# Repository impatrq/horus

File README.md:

<div align="center">
    
# [HORUS](https://linktr.ee/agro_horus)

&nbsp;

| Página web | Email | Instagram | YouTube |
|------------|-------|-----------|---------|
|[agro_horus.app](https://horus-pagina-web.vercel.app)|agroohoruss@gmail.com|[@agro_horus](https://www.instagram.com/agro_horus/)|[agro_horus.video](https://www.youtube.com/watch?v=Mp89aknXm1M&pp=ygUaaG9ydXMgcm9ib3Qgc2VtaWF1dG9tYXRpY28%3D)|

&nbsp;

</div>

## ¿Qué es Horus?
Horus es un robot de reconocimiento para el campo que permite la detección de plagas de manera remota.

## ¿De dónde surgió la idea?

Comenzamos primero con la idea de ayudar al campo, luego de investigación llegamos a las problemáticas que presentaban las plagas artrópodos en las plantaciones, así llegamos a la conclusión de automatizar el monitoreo de plantaciones con un robot autónomo.

## ¿Cómo funciona?
El robot se translada de manera autónoma por el campo y analiza los cultivos a su alrededor con una cámara. La IA del robot analiza el video que percibe con la cámara y determina si se encuentra con una plaga. Esta información es luego transmitida por radiofrecuencia a un módulo de comunicación que permite conectarlo a una computadora con nuestra aplicación. Esto incluye base de datos para guardar las detecciones, interfaz gráfica e interacción con el robot para el usuario

## ¿Quiénes somos?

Somos un grupo de alumnos de E.E.S.T. N°7 "Taller Regional Quilmes" (IMPA).

<div align="center">

</div>

### Cabrera, Martín

* 📧 martincabreracirco@gmail.com

* LinkedIn: https://www.linkedin.com/in/mart%C3%ADn-alejandro-cabrera-6014b727b/

### Contreras, Abril Victoria

* 📷 Instagram: @_ _viicontreras__

* 📧 abrilchiscontreras@gmail.com

* LinkedIn: https://www.linkedin.com/in/abril-contreras-039998303/

### Díaz Steinbrecher, Lara

* 📧 diazsteinbrecher@gmail.com

* LinkedIn: https://www.linkedin.com/in/lara-diaz-steinbrecher-97263b303/

### Ferrante, Santino

* 📧 ferrantesantino14@gmail.com
  
* LinkedIn: https://www.linkedin.com/in/santino-marco-ferrante-a57bb5180/

### Kearney, Mateo

* LinkedIn: https://www.linkedin.com/in/mateo-kearney-996637303/

### Torres, Juan Ignacio

* 📧 juanignaciotorr@gmail.com

* LinkedIn: https://www.linkedin.com/in/juan-ignacio-torres-34a232303/

## Reconocimientos

* Medalla de Oro en PROTOTIPOS - EJE LIBRE de las ONIET 2024

* Medalla de Oro en FEED DE INSTAGRAM de las ONIET 2024

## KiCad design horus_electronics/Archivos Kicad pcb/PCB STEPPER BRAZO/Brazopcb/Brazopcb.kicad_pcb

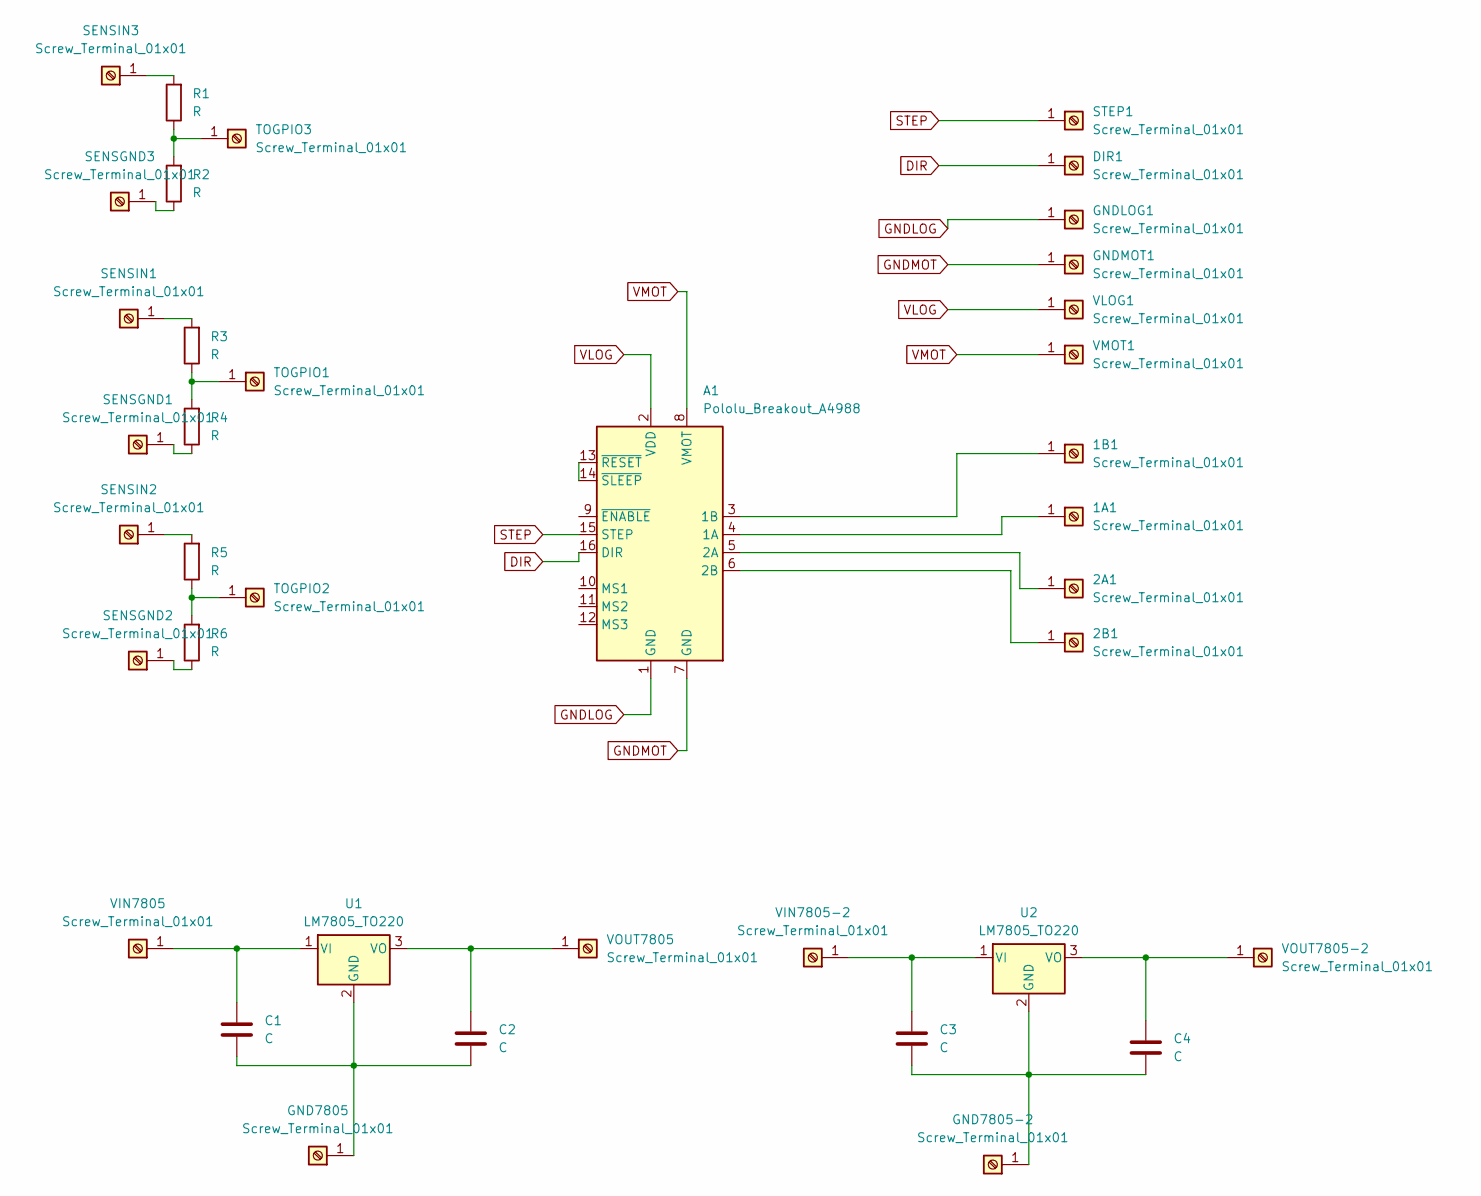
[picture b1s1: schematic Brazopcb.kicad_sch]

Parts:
1A1, 1B1, 2A1, 2B1: Screw_Terminal_01x01; Pin_D1.0mm_L10.0mm
A1: Pololu_Breakout_A4988; Pololu_Breakout-16_15.2x20.3mm
C1, C2, C3, C4: C; R_Axial_DIN0204_L3.6mm_D1.6mm_P5.08mm_Horizontal
DIR1: Screw_Terminal_01x01; Pin_D1.0mm_L10.0mm
GND7805, GND7805-2: Screw_Terminal_01x01; Pin_D1.0mm_L10.0mm
GNDLOG1: Screw_Terminal_01x01; Pin_D1.0mm_L10.0mm
GNDMOT1: Screw_Terminal_01x01; Pin_D1.0mm_L10.0mm
R1, R2, R3, R4, R5, R6: R; R_Axial_DIN0204_L3.6mm_D1.6mm_P7.62mm_Horizontal
SENSGND1, SENSGND2, SENSGND3: Screw_Terminal_01x01; Pin_D1.0mm_L10.0mm
SENSIN1, SENSIN2, SENSIN3: Screw_Terminal_01x01; Pin_D1.0mm_L10.0mm
STEP1: Screw_Terminal_01x01; Pin_D1.0mm_L10.0mm
TOGPIO1, TOGPIO2, TOGPIO3: Screw_Terminal_01x01; Pin_D1.0mm_L10.0mm
U1, U2: LM7805_TO220; TO-220-3_Vertical
VIN7805, VIN7805-2: Screw_Terminal_01x01; Pin_D1.0mm_L10.0mm
VLOG1: Screw_Terminal_01x01; Pin_D1.0mm_L10.0mm
VMOT1: Screw_Terminal_01x01; Pin_D1.0mm_L10.0mm
VOUT7805, VOUT7805-2: Screw_Terminal_01x01; Pin_D1.0mm_L10.0mm

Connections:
DIR: A1.16 (DIR), DIR1.1
GNDLOG: A1.1 (GND), GNDLOG1.1
GNDMOT: A1.7 (GND), GNDMOT1.1
unnamed: 1A1.1, A1.4 (1A)
unnamed: 1B1.1, A1.3 (1B)
unnamed: 2A1.1, A1.5 (2A)
unnamed: 2B1.1, A1.6 (2B)
unnamed: A1.13 (~RESET), A1.14 (~SLEEP)
unnamed: C3.2, C4.2, GND7805-2.1, U2.2 (GND)
unnamed: C1.2, C2.2, GND7805.1, U1.2 (GND)
unnamed: R4.1, SENSGND1.1
unnamed: R6.1, SENSGND2.1
unnamed: R2.1, SENSGND3.1
unnamed: R3.2, SENSIN1.1
unnamed: R5.2, SENSIN2.1
unnamed: R1.2, SENSIN3.1
unnamed: R3.1, R4.2, TOGPIO1.1
unnamed: R5.1, R6.2, TOGPIO2.1
unnamed: R1.1, R2.2, TOGPIO3.1
unnamed: C1.1, U1.1 (VI), VIN7805.1
unnamed: C2.1, U1.3 (VO), VOUT7805.1
unnamed: C3.1, U2.1 (VI), VIN7805-2.1
unnamed: C4.1, U2.3 (VO), VOUT7805-2.1
STEP: A1.15 (STEP), STEP1.1
VLOG: A1.2 (VDD), VLOG1.1
VMOT: A1.8 (VMOT), VMOT1.1

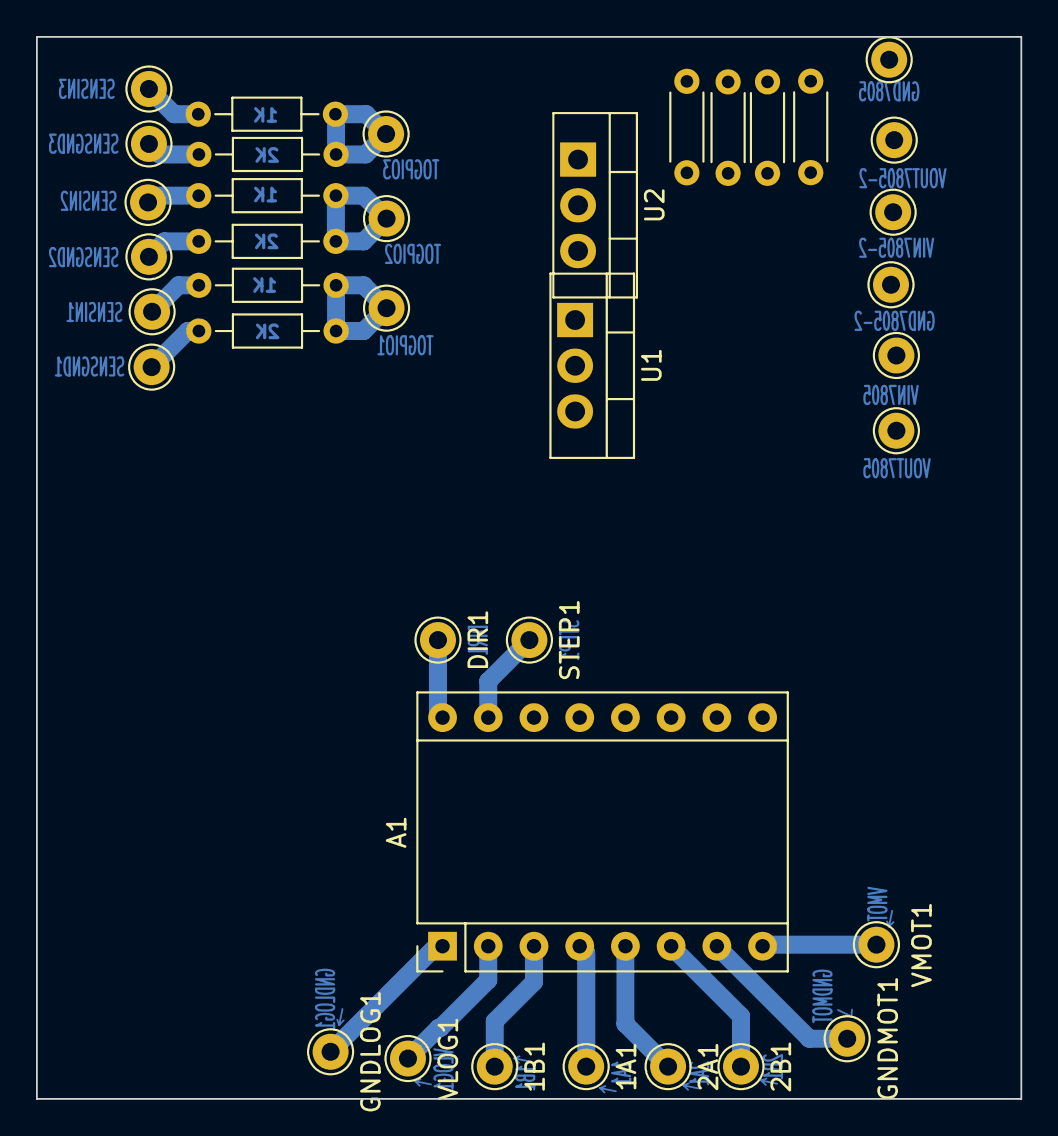
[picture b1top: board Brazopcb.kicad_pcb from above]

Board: 2 copper layers, 54.7 x 59.0 mm, 38 parts (0 on the bottom side), 26 nets.

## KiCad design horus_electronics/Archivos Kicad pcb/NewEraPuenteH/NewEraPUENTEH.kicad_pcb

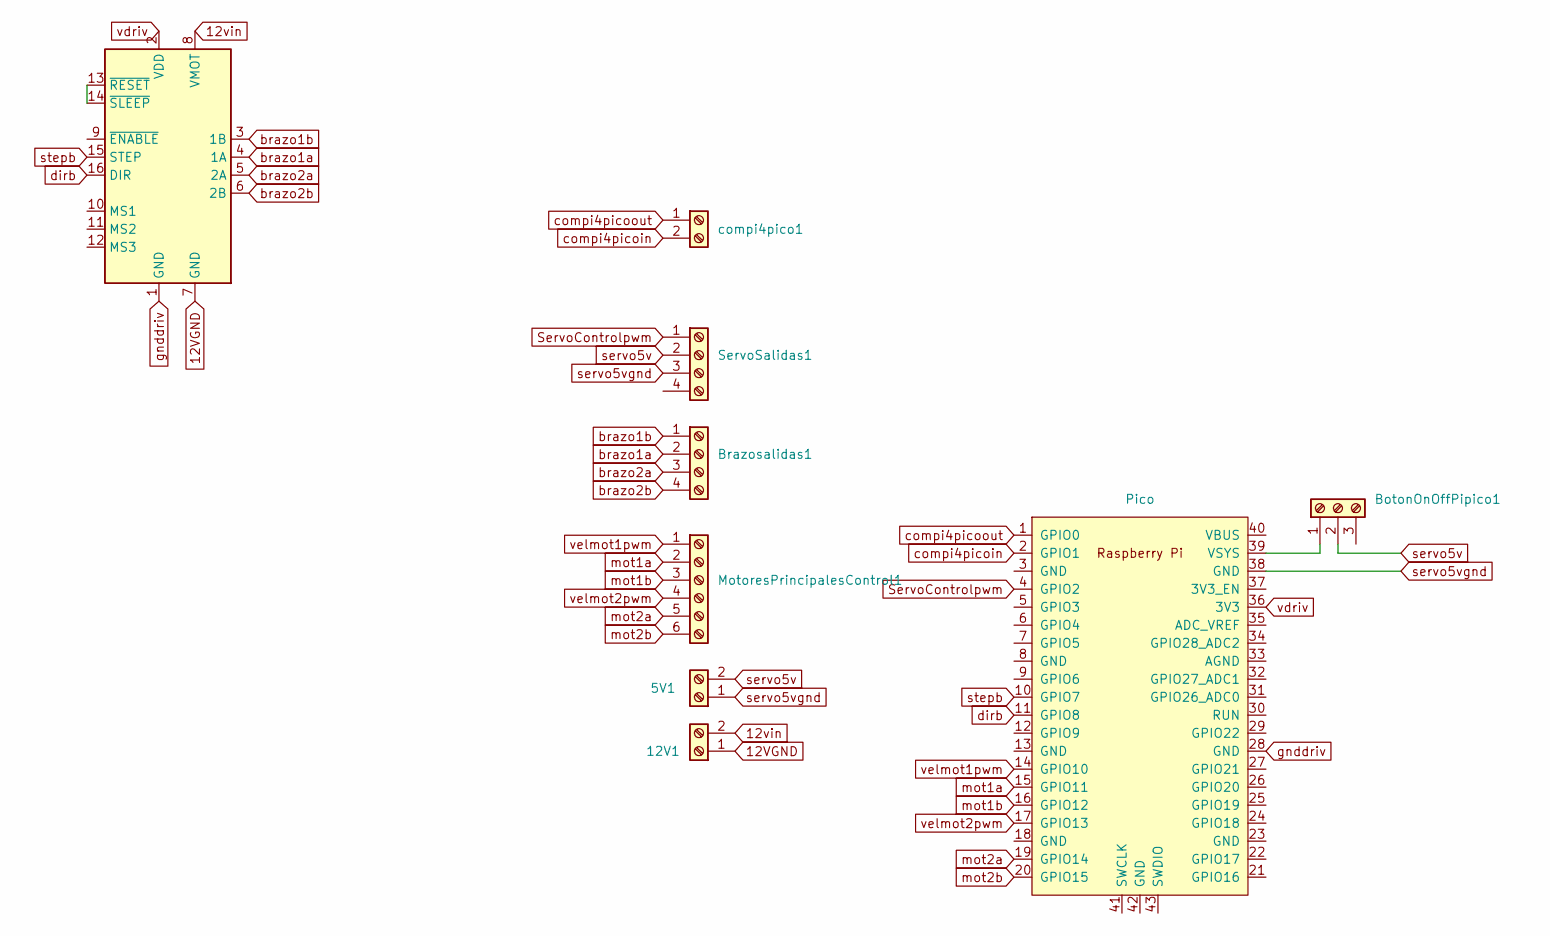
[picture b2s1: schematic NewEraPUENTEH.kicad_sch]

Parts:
5V1, 12V1: Screw_Terminal_01x02; TerminalBlock_Phoenix_MKDS-1,5-2-5.08_1x02_P5.08mm_Horizont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
A1: Pololu_Breakout_A4988; Pololu_Breakout-16_15.2x20.3mm
BotonOnOffPipico1: Screw_Terminal_01x03; Altech_AK300_1x03_P5.00mm_45-Degree
Brazosalidas1: Screw_Terminal_01x04; TerminalBlock_Phoenix_MKDS-1,5-4-5.08_1x04_P5.08mm_Horizont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
MotoresPrincipalesControl1: Screw_Terminal_01x06; TerminalBlock_Phoenix_MKDS-1,5-6-5.08_1x06_P5.08mm_Horizont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
ServoSalidas1: Screw_Terminal_01x04; TerminalBlock_Phoenix_MKDS-1,5-4-5.08_1x04_P5.08mm_Horizont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
U1: Pico; RPi_Pico_SMD_TH
compi4pico1: Screw_Terminal_01x02; TerminalBlock_Phoenix_MKDS-1,5-2-5.08_1x02_P5.08mm_Horizont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

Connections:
12VGND: 12V1.1, A1.7 (GND)
12vin: 12V1.2, A1.8 (VMOT)
unnamed: A1.13 (~RESET), A1.14 (~SLEEP)
unnamed: BotonOnOffPipico1.1, U1.39 (VSYS)
ServoControlpwm: ServoSalidas1.1, U1.4 (GPIO2)
brazo1a: A1.4 (1A), Brazosalidas1.2
brazo1b: A1.3 (1B), Brazosalidas1.1
brazo2a: A1.5 (2A), Brazosalidas1.3
brazo2b: A1.6 (2B), Brazosalidas1.4
compi4picoin: U1.2 (GPIO1), compi4pico1.2
compi4picoout: U1.1 (GPIO0), compi4pico1.1
dirb: A1.16 (DIR), U1.11 (GPIO8)
gnddriv: A1.1 (GND), U1.28 (GND)
mot1a: MotoresPrincipalesControl1.2, U1.15 (GPIO11)
mot1b: MotoresPrincipalesControl1.3, U1.16 (GPIO12)
mot2a: MotoresPrincipalesControl1.5, U1.19 (GPIO14)
mot2b: MotoresPrincipalesControl1.6, U1.20 (GPIO15)
servo5v: 5V1.2, BotonOnOffPipico1.2, ServoSalidas1.2
servo5vgnd: 5V1.1, ServoSalidas1.3, U1.38 (GND)
stepb: A1.15 (STEP), U1.10 (GPIO7)
vdriv: A1.2 (VDD), U1.36 (3V3)
velmot1pwm: MotoresPrincipalesControl1.1, U1.14 (GPIO10)
velmot2pwm: MotoresPrincipalesControl1.4, U1.17 (GPIO13)

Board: 2 copper layers, 9 parts (0 on the bottom side), 23 nets, no tracks yet.

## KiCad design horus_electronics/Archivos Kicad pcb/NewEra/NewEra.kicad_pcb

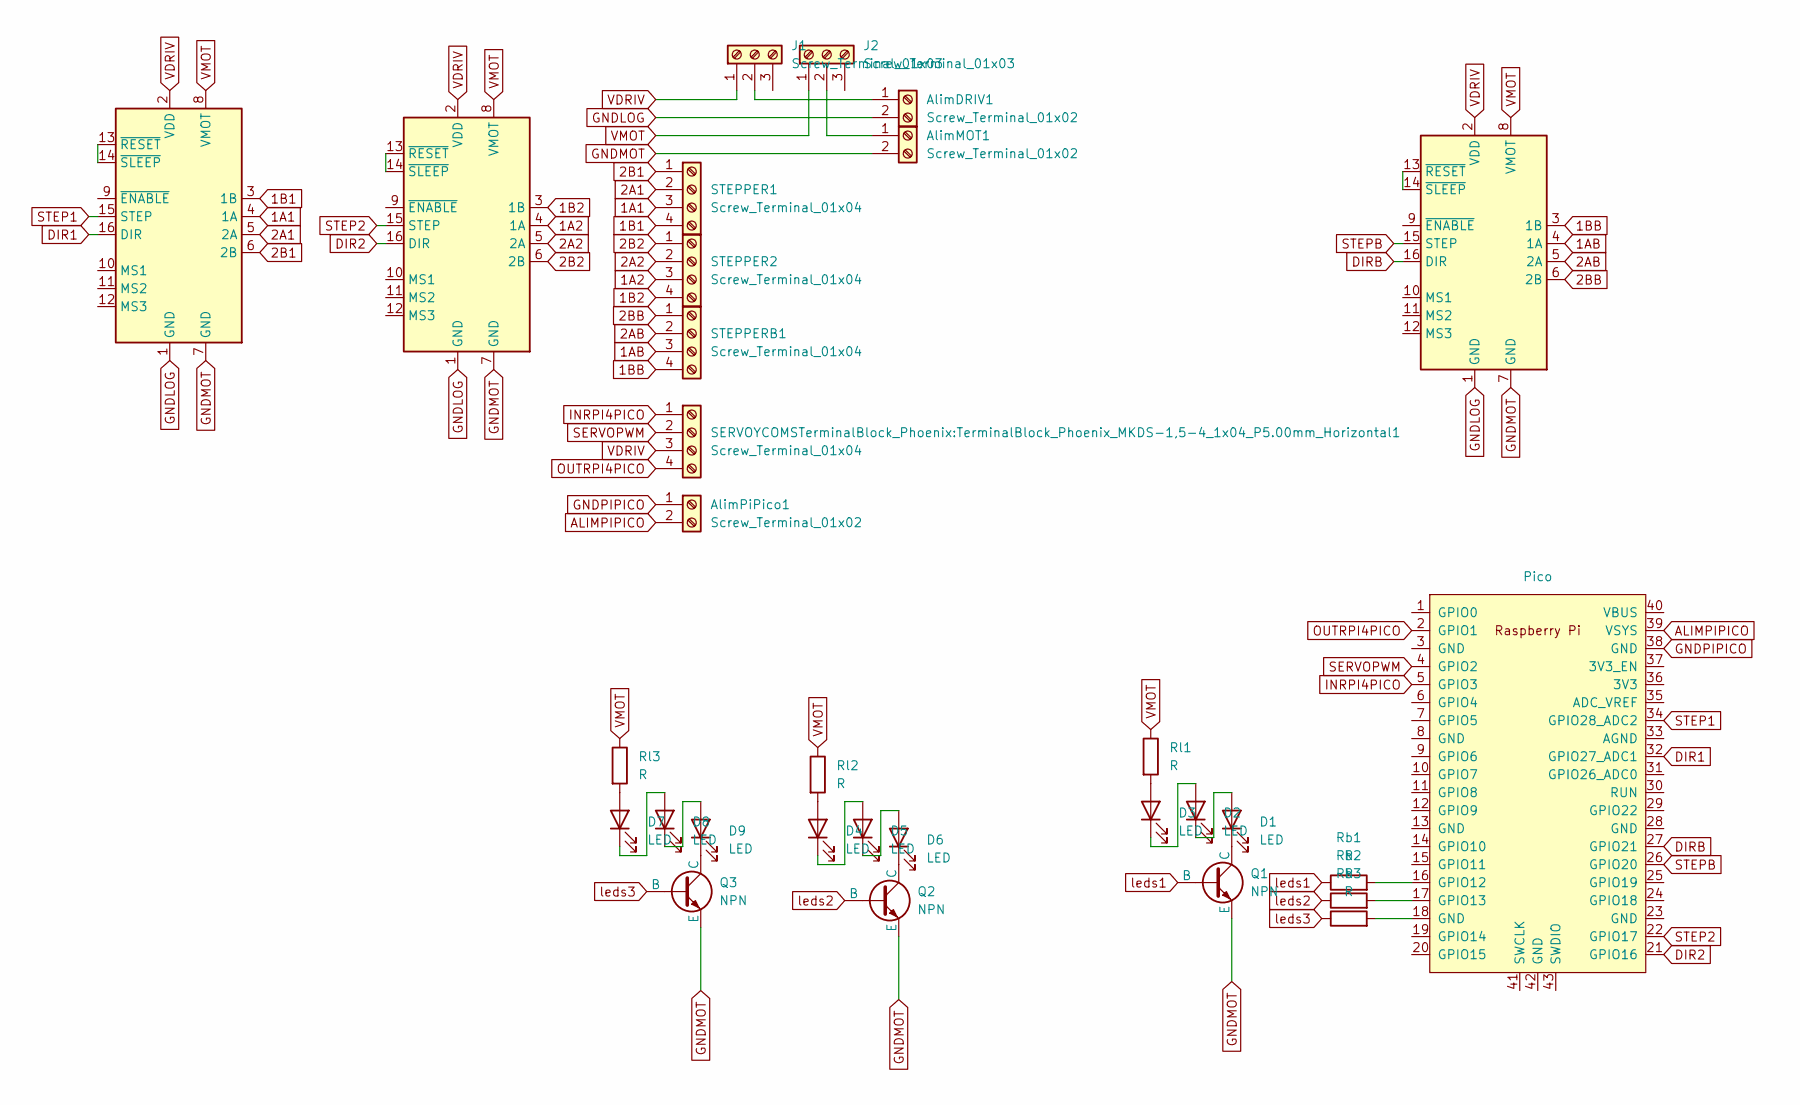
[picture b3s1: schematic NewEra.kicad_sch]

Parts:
A1, A2, A3: Pololu_Breakout_A4988; Pololu_Breakout-16_15.2x20.3mm
AlimDRIV1: Screw_Terminal_01x02; TerminalBlock_Phoenix_MKDS-1,5-2-5.08_1x02_P5.08mm_Horizont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
AlimMOT1: Screw_Terminal_01x02; TerminalBlock_Phoenix_MKDS-1,5-2-5.08_1x02_P5.08mm_Horizont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
AlimPiPico1: Screw_Terminal_01x02; TerminalBlock_Phoenix_MKDS-1,5-2-5.08_1x02_P5.08mm_Horizont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
D1, D2, D3, D4, D5, D6, D7, D8, D9: LED; LED_D1.8mm_W1.8mm_H2.4mm_Horizontal_O1.27mm_Z1.6mm
J1, J2: Screw_Terminal_01x03; Altech_AK300_1x03_P5.00mm_45-Degree
Q1, Q2, Q3: NPN; TO-92_HandSolder
Rb1, Rb2, Rb3: R; R_Axial_DIN0204_L3.6mm_D1.6mm_P5.08mm_Horizontal
Rl1, Rl2, Rl3: R; R_Axial_DIN0204_L3.6mm_D1.6mm_P5.08mm_Horizontal
SERVOYCOMSTerminalBlock_Phoenix:TerminalBlock_Phoenix_MKDS-1,5-4_1x04_P5.00mm_Horizontal1: Screw_Terminal_01x04; TerminalBlock_Phoenix_MKDS-1,5-4-5.08_1x04_P5.08mm_Horizont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
STEPPER1, STEPPER2: Screw_Terminal_01x04; TerminalBlock_Phoenix_MKDS-1,5-4-5.08_1x04_P5.08mm_Horizont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
STEPPERB1: Screw_Terminal_01x04; TerminalBlock_Phoenix_MKDS-1,5-4-5.08_1x04_P5.08mm_Horizont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
U1: Pico; RPi_Pico_SMD_TH

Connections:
1A1: A1.4 (1A), STEPPER1.3
1A2: A2.4 (1A), STEPPER2.3
1AB: A3.4 (1A), STEPPERB1.3
1B1: A1.3 (1B), STEPPER1.4
1B2: A2.3 (1B), STEPPER2.4
1BB: A3.3 (1B), STEPPERB1.4
2A1: A1.5 (2A), STEPPER1.2
2A2: A2.5 (2A), STEPPER2.2
2AB: A3.5 (2A), STEPPERB1.2
2B1: A1.6 (2B), STEPPER1.1
2B2: A2.6 (2B), STEPPER2.1
2BB: A3.6 (2B), STEPPERB1.1
ALIMPIPICO: AlimPiPico1.2, U1.39 (VSYS)
DIR1: A1.16 (DIR), U1.32 (GPIO27_ADC1)
DIR2: A2.16 (DIR), U1.21 (GPIO16)
DIRB: A3.16 (DIR), U1.27 (GPIO21)
GNDLOG: A1.1 (GND), A2.1 (GND), A3.1 (GND), AlimDRIV1.2
GNDMOT: A1.7 (GND), A2.7 (GND), A3.7 (GND), AlimMOT1.2, Q1.3 (E), Q2.3 (E), Q3.3 (E)
GNDPIPICO: AlimPiPico1.1, U1.38 (GND)
INRPI4PICO: SERVOYCOMSTerminalBlock_Phoenix:Termina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.1, U1.5 (GPIO3)
unnamed: A1.13 (~RESET), A1.14 (~SLEEP)
unnamed: A2.13 (~RESET), A2.14 (~SLEEP)
unnamed: A3.13 (~RESET), A3.14 (~SLEEP)
unnamed: AlimDRIV1.1, J1.2
unnamed: AlimMOT1.1, J2.2
unnamed: D1.2 (A), D2.1 (K)
unnamed: D1.1 (K), Q1.1 (C)
unnamed: D2.2 (A), D3.1 (K)
unnamed: D3.2 (A), Rl1.2
unnamed: D4.2 (A), Rl2.2
unnamed: D4.1 (K), D5.2 (A)
unnamed: D5.1 (K), D6.2 (A)
unnamed: D6.1 (K), Q2.1 (C)
unnamed: D7.2 (A), Rl3.2
unnamed: D7.1 (K), D8.2 (A)
unnamed: D8.1 (K), D9.2 (A)
unnamed: D9.1 (K), Q3.1 (C)
unnamed: Rb3.2, U1.18 (GND)
unnamed: Rb1.2, U1.16 (GPIO12)
unnamed: Rb2.2, U1.17 (GPIO13)
OUTRPI4PICO: SERVOYCOMSTerminalBlock_Phoenix:Termina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.4, U1.2 (GPIO1)
SERVOPWM: SERVOYCOMSTerminalBlock_Phoenix:Termina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.2, U1.4 (GPIO2)
STEP1: A1.15 (STEP), U1.34 (GPIO28_ADC2)
STEP2: A2.15 (STEP), U1.22 (GPIO17)
STEPB: A3.15 (STEP), U1.26 (GPIO20)
VDRIV: A1.2 (VDD), A2.2 (VDD), A3.2 (VDD), J1.1, SERVOYCOMSTerminalBlock_Phoenix:Termina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.3
VMOT: A1.8 (VMOT), A2.8 (VMOT), A3.8 (VMOT), J2.1, Rl1.1, Rl2.1, Rl3.1
leds1: Q1.2 (B), Rb1.1
leds2: Q2.2 (B), Rb2.1
leds3: Q3.2 (B), Rb3.1

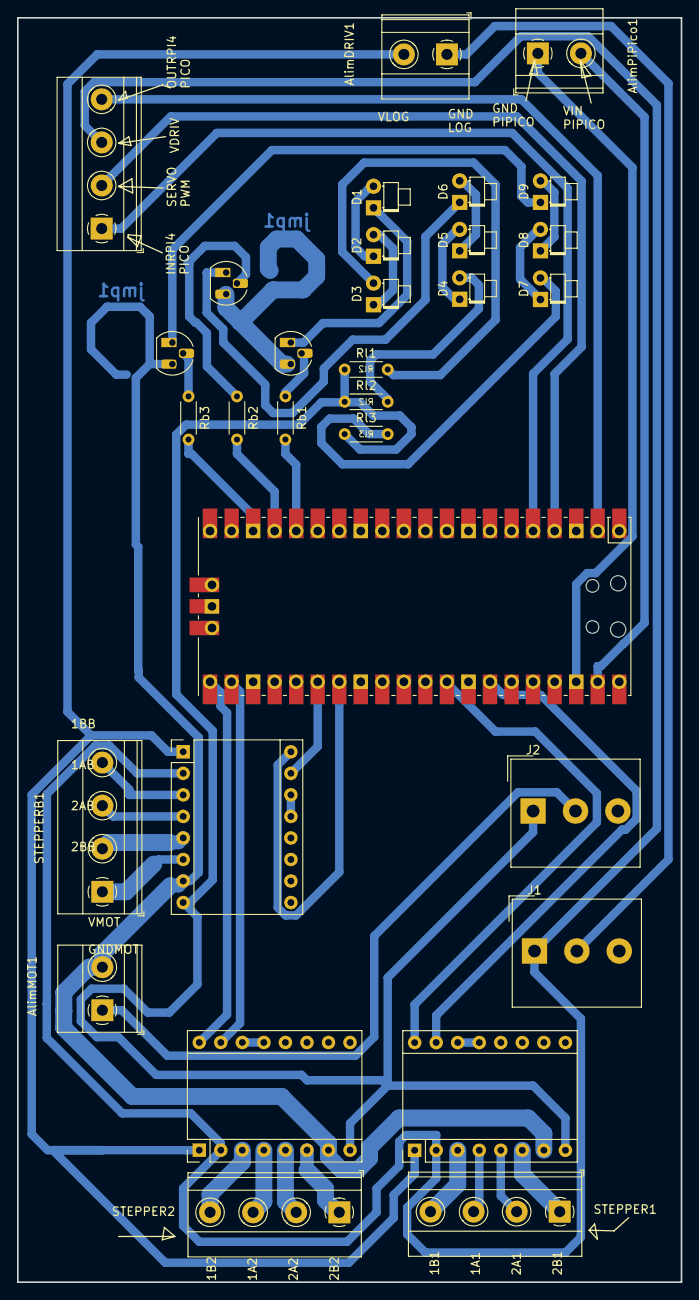
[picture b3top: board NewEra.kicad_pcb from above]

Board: 2 copper layers, 78.3 x 149.1 mm, 31 parts (0 on the bottom side), 50 nets.

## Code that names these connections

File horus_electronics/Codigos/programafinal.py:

#Importo Librerías a usar
from machine import Pin, PWM
from time import sleep

# Configuración de los pines GPIO para los motores DC con Puente H
velmot1pwm = PWM(Pin(10))
velmot2pwm = PWM(Pin(13))
mot1a = Pin(11, Pin.OUT)   # pin 2b del motor 1
mot1b = Pin(12, Pin.OUT)
mot2a = Pin(14, Pin.OUT)   # pin 2a del motor 2
mot2b = Pin(15, Pin.OUT)

# Configurar la frecuencia de PWM (suele ser 1kHz para motores DC)
velmot1pwm.freq(1000)
velmot2pwm.freq(1000)

# Pines de control del brazo tijera y el servo
dirB = Pin(8, Pin.OUT)   # Dirección del motor del brazo
stepB = Pin(7, Pin.OUT)  # Paso del motor del brazo
servo_pin = Pin(2)       # Pin para el control del servo (sin .OUT para PWM)

# Configuración del PWM para el servomotor
servo_pwm = PWM(servo_pin)  # Configurar pin 2 como salida PWM
servo_pwm.freq(50)          # Frecuencia de 50Hz (20 ms de período)

# Función para controlar un motor paso a paso con A4988 (usada para el brazo)
def mover_stepper(dir_pin, step_pin, pasos, direccion, delay):
    dir_pin.value(direccion)
    for _ in range(pasos):
        step_pin.on()
        sleep(delay)
        step_pin.off()
        sleep(delay)

# Función para controlar dos motores paso a paso de forma simultánea con A4988
def mover_steppers_simultaneos(dir_pin1, step_pin1, dir_pin2, step_pin2, pasos, direccion, delay):
    dir_pin1.value(direccion)
    dir_pin2.value(direccion)
    for _ in range(pasos):
        step_pin1.on()
        step_pin2.on()
        sleep(delay)
        step_pin1.off()
        step_pin2.off()
        sleep(delay)

# Función principal para ejecutar la secuencia
def detectar_pulso():
    esperar_pulso("Iniciar secuencia")
    pulsostartrecibido()

def pulsostartrecibido():
    print("Arrancando motores de orugas...")
    mover_steppers_simultaneos(dir1, step1, dir2, step2, pasos=200, direccion=1, delay=0.002)
    print("Motores funcionando durante 1 segundo...")
    sleep(1)
    brazoup()

def brazoup():
    print("Levantando brazo hasta el tope...")
    mover_stepper(dirB, stepB, pasos=600, direccion=1, delay=0.01)
    esperapulsocamara()

def esperapulsocamara():
    esperar_pulso("Esperando pulso de la cámara")
    pulsocamararecibido()

def pulsocamararecibido():
    print("Iniciando paneo del servo...")
    mover_servo_paneo()
    terminaservo()

# Control del servo para paneo de 0 a 180 grados en intervalos de 30 grados y luego regresar
def mover_servo_paneo():
    print("Moviendo el servo de 0 a 180 grados en intervalos de 30 grados...")
    for angulo in range(0, 181, 30):
        mover_servo(angulo)
        sleep(0.5)
    
    print("Moviendo el servo de 180 a 0 grados en intervalos de 30 grados...")
    for angulo in range(180, -1, -30):
        mover_servo(angulo)
        sleep(0.5)

# Función para mover el servo a una posición específica usando PWM real
def mover_servo(angulo):
    # Convertir el ángulo a ciclo de trabajo PWM
    duty_cycle = angle_to_duty_cycle(angulo)
    servo_pwm.duty_u16(duty_cycle)  # Ajustar ciclo de trabajo
    print(f"Servo movido a {angulo} grados con ciclo de trabajo {duty_cycle}")

# Función para convertir un ángulo (0-180) a ciclo de trabajo PWM
def angle_to_duty_cycle(angulo):
    # El ciclo de trabajo para el servo varía de 1ms (0 grados) a 2ms (180 grados).
    # En términos de ciclo de trabajo para una señal de 50 Hz:
    # - 1 ms corresponde aproximadamente a un ciclo de trabajo de 5% (3276 en valor de 16 bits)
    # - 2 ms corresponde aproximadamente a un ciclo de trabajo de 10% (6553 en valor de 16 bits)
    # Mapear el rango 0-180 grados al rango 3276-6553
    min_duty = 3276   # 5% de ciclo de trabajo (1 ms)
    max_duty = 6553   # 10% de ciclo de trabajo (2 ms)
    return int(min_duty + (angulo / 180.0) * (max_duty - min_duty))

def terminaservo():
    print("Enviando pulso a la Raspberry Pi 4...")
    sleep(3)
    print("Esperando 3 segundos...")
    brazodown()

def brazodown():
    print("Bajando brazo hasta el tope...")
    mover_stepper(dirB, stepB, pasos=600, direccion=0, delay=0.002)
    movermotoresfinal()

def movermotoresfinal():
    print("Moviendo los motores de orugas nuevamente...")
    mover_steppers_simultaneos(dir1, step1, dir2, step2, pasos=200, direccion=1, delay=0.01)
    print("Movimiento finalizado. Programa concluido.")

def esperar_pulso(mensaje):
    while True:
        pulso = input(f"{mensaje} (Escribe '1' para enviar pulso): ")
        if pulso == '1':
            print("Pulso detectado.")
            return
        else:
            print("Pulso no detectado, esperando...")

# Iniciar la simulación
detectar_pulso()

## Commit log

2024-04-22 App first commit
    Adding template
2024-04-22 Header (base)
    Componente Header base terminado
2024-04-30 feat: conexión del backend con la base de datos de mangodb
    chore: se dividió la app en una carpeta de frontend (que contiene el código previo) y una de backend.
    Se agregó una carpeta de modelos con un esquema para la base de datos.
2024-04-30 doc: add readme file
2024-04-30 chore: agregando la carpeta de backend
2024-04-30 fix: elimino submodulo
2024-04-30 feat: conexion con mongodb
2024-04-30 chore: ignoro modulos y .env
2024-04-30 chore: esquema para mongodb
2024-04-30 chore: modulos para nodejs
2024-05-10 feat: Indicacion de uso de archivo
2024-05-10 feat: Carpeta Yolov5s
2024-05-10 docs: especificacion de uso
2024-05-10 Rename READ.me to README.md
2024-05-17 feat: agrego comunicación serie entre raspberry pico y servidor node
2024-05-20 feat: añado rutas y metodos para comunicación con base de datos
2024-05-22 patch: resuelvo error de conexión con base de datos
2024-05-22 feat: Codigos varios de prueba
2024-05-22 feat: conexion con archivo capturador json
2024-05-22 docs: facilitar codigo
2024-05-22 feat: dataset inicial orugas
2024-05-22 feat: documentacion varia
2024-05-22 README.md actualizado
2024-05-23 patch: resuelvo error en la comunicación con la base de datos
2024-05-31 feat: implementación de electron patch: solución de error de concurrently
2024-05-31 patch: resuelvo error al iniciar electron
2024-06-10 feat: Creación de los views y html de la página. Css de Contacts
2024-06-26 feat: Agrego la página de Contactos terminada
2024-07-10 docs: Subo Anteproyecto, Historias de Usuario y Carpeta de Campo por primera vez
2024-07-31 Resuelvo error en terminaciones no identificados de los paquetes de json en el puerto serial
2024-07-31 fix: Resuelvo error para el cambio de ramas
2024-07-31 fix: Cambio de ramas (parte del commit anterior)
2024-07-31 fix: Resuelvo error con la terminación de los paquetes json en la comunicación serial
2024-08-02 feat: Agregando rutas de comunicación al index.js en vez de archivos separados
2024-08-16 feat: Agrego inputs diferentes por cada dato por el que filtrar
2024-08-19 feat: Agrego sección para ordenar filtros
2024-08-21 feat: Agrego selección y eliminación de cada categoría de filtro en ruta de data
2024-08-25 feat: Filtro con una sola categoría (date) funciona correctamente
2024-08-28 Agrego filtro para más de una categoría junto con reset del filtro
2024-08-28 feat: Agrego pagina terminada
2024-08-28 Create test
2024-08-28 create folder
2024-08-28 chore: Borro Hoja de mi tercer personaje
2024-08-29 feat: Cambio de imagen de seccion de sponsor
2024-08-29 Ft: todo
2024-08-29 feat: build para deployment
2024-08-29 chore: Agrego elementos restantes para el deployment
2024-09-02 feat: Agrego filtro por orden de la ruta de data
2024-09-04 fix: Arreglo orden para que inicie bien electron
2024-09-04 chore: Actualización de imagen de marito
2024-09-04 chore: Modificacion para adaptacion de resolucion en 700px
2024-09-04 docs: Actualizo README.md con información general
2024-09-04 Actualizo correctamente la información general del README.md
2024-09-04 docs Centralizo titulo del titulo del README.md
2024-09-04 docs: Remuevo contorno de la imagen del logo y lo centro
2024-09-07 Actualizo link de la página web hosteada
2024-09-07 Arreglo error en el link de la pagina
2024-09-07 Revert "Arreglo error en el link de la pagina"
    This reverts commit f95c78b9b8c9a3abc59088f820d1c37c3e927f38.
2024-09-07 docs: Arreglo error en el link de la pagina
2024-09-21 Agrego templates de los perfiles para los robots y un boton para agregar (no script)
2024-09-24 Feat: Modelos de la IA hasta ahora
2024-09-24 Feat: Datasets de las versiones 1 y 1.5
2024-09-30 feat Agrego ruta de Galería
2024-10-02 feat: agrago elemento de mapa para la home route de la libreria de leaflet para vue
2024-10-02 fix: Resuelvo problema con el mensaje que ocurre cuando no hay imagenes subidas
2024-10-02 docs: Agrego archivo de banner y de presentación
2024-10-02 feat: Agrego input para zoom del mapa
2024-10-08 chore: Cambio el idioma de los elementos de la interfaz a español
2024-10-08 feat: Agrego estructura del mapa en la ruta de Home en el frontend (mapa,capas, marcadores, filtro), agrego una ruta en la api para pedir las coordenadas de todos los logs, agrego un esquema para dat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
2024-10-08 fix: Agrego parte de homeview faltante de la estructura
2024-10-21 todo
    Archivos y imagenes estructura
2024-10-22 Preupdate
2024-10-22 Create Estructura Horus
    todo
2024-10-22 Update: KICADPCB folder
2024-10-22 Update All Folders from Local Rep
2024-10-22 Create Estructura HORUS
2024-10-22 fix Subi mal el archivo
2024-10-22 fix lo volvi a subir mal
2024-10-22 Create New Directory
2024-10-22 Create Archivo
2024-10-22 feat: "Añado Archivos Estructurales de HORUS"
2024-10-22 feat: "Añado Archivos .F3D de la Estructura de HORUS"
2024-10-22 feat: "Añado Archivos .STL de la Estructura de HORUS"
2024-10-22 feat: "Añado imagenes de Modelado de Estructura de HORUS"
2024-10-22 feat:añodo imagenes de "primeros prototipos de HORUS"
2024-10-22 Delete Estructura Horus.rar
    subido por error
2024-10-22 feat: pesos y dimensiones de componentes
2024-10-28 docs: Agrego Informe presentado en la competenci feed de instagram de las ONIET
2024-10-31 Codigo del robot
2024-11-01 docs: Agrego manual de usuario
2024-11-01 banner horus corregido
2024-11-01 Update README.md reconocimiento prototipos
2024-11-01 Update README.md reconocimiento feed de ig
2024-11-01 docs: Agrego Carpeta Tecnica
2024-11-04 docs: Subo Carpeta de Campo actualizada y con el nombre correcto
2024-11-04 docs: Elimino Carpeta de Campo desactualizada y con un nombre que no cumple con las normas establecidas
2024-11-04 docs: Subo Carpeta de Campo actualizada hasta el 4/11
2024-11-07 Fix: Se añadió sin sobreescribirse
2024-11-07 Feat: Actualizo carpeta de Imagenes
2024-11-07 Feat: Actualizo Carpeta de Gerbers
2024-11-07 Feat: UpToDate Carpeta PCBS kicad
2024-11-07 Fix: Borro .test
2024-11-07 Feat: Añado Placa Multipurpose
    Añado Placa multipurpose con Modificación inesperada para ser usada con Puente H, Fuí notificado de este cambio a menos de una semana del Cierre de prerequisitos y presentación de mvp
2024-11-07 subo parte de tapa superior
2024-11-07 soporte de nuevos motore
2024-11-07 subo carcasa de arriba horus
2024-11-07 soporte de motores nuevos
2024-11-08 docs: Subo Carpeta Técnica con información actualizada
    Agregamos información en el capítulo de Introducción, Sistema de Comunicación, Aplicación y IA
2024-11-08 feat: Agrego el resto de funcionalidades al mapa, e integro los perfiles de robot con servidor
    Al mapa se agregó la funcionalidad de offline como control en el propio mapa, la funcionalidad para agregar zonas de deteccion y puntos de partida aparte de las trampas, y ahora los tres marcadores s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
    El servidor ahora tiene funcionalidades para reicibir apropiadamente de la conexi
2024-11-10 feat: Agrego eliminacion para elementos al ingresarlos y cambia las trampas a circulos
2024-11-10 feat: Integro los círculos (trampas) al backend y agrego funcionalidad offline (por pendrive)
2024-11-10 Docs: Comento el codigo
2024-11-10 feat: Agrego colores personalizados al mapa
2024-11-10 fix: soluciono error de alerts y agrego indicacion visual por error (Home)
2024-11-11 feat: programa main del robot
2024-11-11 HORUS - Informe Descriptivo
2024-11-11 docs: HORUS - SysAPP
2024-11-11 Update README.md (video horus)
2024-11-11 docs: speech video HORUS
2024-11-11 docs: Carpeta Técnica, Introducción con texto completo
    Completé infromación de adaptabilidad, objetivo, innovación, alcance y beneficios. Adjunté graficos
2024-11-12 feat: main auxiliar y cambios en detect.py desde la raspberry
2024-11-18 feat: Actualizo el codigo del modulo comunicador con codigo de los Lora
2024-11-18 fix: corrigo error en la creación de perfiles de robot
2024-11-18 fix: Agrego marcador violeta para robots (mapa)
2024-11-18 fix: agrego marcador violeta para robots del mapa
2024-11-18 Agrego diferentes colores para indicadores del mapa
2024-11-18 fix: Arreglo error en el selector de trampa de feromona (filtro)
2024-11-18 feat: cambio css en las diferentes (sombras más que nada)
2024-11-19 feat: Agrego scripts para que se pueda iniciar la app como ejecutable
2024-11-19 chore: agrego package-lock.json con cambios
2024-11-19 feat: preparo la branch para release
2024-11-19 feat: agrego Readme.md con instrucciones
2024-11-19 feat: agrego fotos para el readme.md que faltaban
2024-11-19 fix: ajusto el ancho de las imagenes (readme.md)
2024-11-19 feat: Agrego nuevo readme.md para la app (originalmente de release
2024-11-19 fix: Error de requerimientos en readme
2024-11-19 fix: corrigo error de requerimientos en readme.md (app)
2024-11-19 fix: Le quito animacion de zoom al mapa para evitar errores
2024-11-20 fix: Arreglo problema con el muestreo de nuevos perfiles
2024-11-21 feat: agrego que se inserte el dia y hora desde la app y no desde el robot
2024-11-21 fix: Arreglo error de las imágenes al hacerles zoom (descentradas)
2024-11-23 Feat: programa de gps
2024-11-23 Feat: programa de prueba para la camara
2024-11-23 Feat: main_auxiliar funcional con pendrive
2024-11-23 README.md ACTUALIZO VIDEO DE YOUTUBE
2024-11-23 subo carpeta tecnica actualizada hasta el 23/11
2024-11-23 subo carpeta de campo actualizada hasta el 23/11
2024-11-23 subo manual de usuario 23/11
2024-11-25 feat subo archivo stl de tensor final
2024-11-25 feat subo archivo de modelado tensor definitivo
2024-11-25 docs: Subo carpeta técnica con capítulos actualizados
    Capítulos de Placa Receptora y Página Web actualizados
2024-11-25 docs: Subo Carpeta Técnica con capítulos actualizados
    Actualizo capítulo de Placa Receptora y de Página Web
2024-11-25 chore: borro Carpeta Técnica mal subida
    Subí la carpeta técnica en un lugar que no debía, ya la saco
2024-11-25 Fix: carpeta clonada a la raspberry 4 y archivos actualizados a los actuales dentro de la raspberry
2024-11-25 docs: Subo Carpeta de Campo actualizada hasta el 25/11
2024-11-25 Feat: programa de gps implementado al mainaxuliar.py
2024-11-26 docs: actualizacion hasta el 25/11
2024-11-26 docs: Subo MVP
2024-11-27 docs: Subo compras de todos los componentes
2024-11-27 docs: agrego archivo de elementos inconclusos de HORUS
2024-11-27 docs: agrego comprobantes de compras 15/11
2024-11-27 docs: agrego comprobante de compra 10/10
2024-11-27 docs: agrego comprobante de compra 4/10
2024-11-27 docs: agrego comprobante de compra 24/9
2024-11-27 docs: agrego comprobante de compra 14/10
2024-11-27 docs: agrego comprobante de compra 30/9
2024-11-27 docs: subo foto del equipo
2024-11-27 docs: subo foto de HORUS
2024-11-27 docs:
2024-11-27 docs: agrego comprobante de medalla de prototipos
2024-11-27 docs: Tabla de costos completa
    Subo el archivo con precios parciales e individuales, en dólares y pesos, y ordenados de forma alfabética de todos los elementos comprados
2024-11-28 docs: Tabla de costos completa corregida
    Actualizo la tabla de todos los costos que requeriría recrear un robot Horus
2024-11-28 docs: Tabla de costos completa corregida
    Subo la tabla de costos corregida en formato pdf
2024-12-13 docs: Agrego foto de equipo a readme.md
2024-12-13 docs: Ajusto el tamaño de la imagen del grupo en el readme.md
